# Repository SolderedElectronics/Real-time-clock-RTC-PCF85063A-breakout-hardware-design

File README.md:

# Real time clock RTC PCF85063A breakout Hardware Design

## About the Product

|  |
| :----------------------------------------------------------: |
| [Buy Real time clock RTC PCF85063A breakout](https://www.solde.red/333051) |

RTC (Real Time Clock) is a device that carefully and precisely tracks time and dates. It is extremely precise, so it is more suitable for long-term time tracking than clocks on microcontrollers. This breakout can work with an extremely low current and thanks to the alarm feature and interrupt pin, it will allow a microcontroller to enter sleep mode until its awaken by this RTC.

It has a built-in battery holder (battery not included) and even if power is lost, real-time tracking won’t be affected.

---

## Repository Contents

This repository contains all design files for Real time clock RTC PCF85063A breakout, organized as follows:

- **`CAD` folder**: Contains KiCAD design files, including:
  - Schematics
  - PCB layout
  - Panel PCB layout
  - Source 3D files in Fusion360, if any
  - All files are sorted by version with a detailed change log.
- **`OUTPUTS` folder**: Includes all production-ready files, such as:
  - Bill of Materials (BOM) and interactive BOM (iBOM)
  - PDF versions of schematics
  - 3D `.step` file of the board
  - 3D-printable models
  - Gerber files for PCB manufacturing
  - Image of the pinout of the board
  - Product image
  - Compliance, legal and generic sales documents

Refer to the `Change Log` in the CAD folder for details about updates between versions.

---

## Learn More About the Product

Beyond the repository, explore the following resources:

### Soldered Verify

The **Soldered Verify** system ensures every board you purchase from Soldered is fully functional. It also provides access to exclusive test data for your product. To get started, find the unique Soldered Verify ID on your product's packaging and enter the ID on the [Soldered Verify page](https://soldered.com/verify/) to access test results and additional product details.

### Soldered Community

Soldered Community is your go-to place for technical support. Our engineers track and answer all questions posted there, and it’s a great space for the maker community. Get answers to your questions and solutions for your challenges at [Soldered Community](https://soldered.com/community).

### solde.red

solde.red is an ultimate URL shortener and information hub. Access it by typing solde.red/ followed by your product SKU, e.g., [solde.red/333000](https://solde.red/333000), to find getting-started guides, datasheets, open-source hardware and software files, certifications, images, pinouts, and more. Read more about the shortener [here](https://solde.red/info/).

---

## Contributing

Contributions are welcome! Here’s how you can get involved:

- Submit pull requests to enhance the design or fix issues.
- Report bugs or problems by opening an issue.

We encourage community collaboration to make this product even better.

---

## About Soldered

[Soldered for Makers](https://soldered.com) specializes in designing and manufacturing electronic products tailored for enthusiasts, ranging from hobbyists to professionals. Our portfolio includes electronic boards, sensors, and actuators that are widely utilized in fields such as microelectronics, mechatronics, robotics, programming, and IoT. Every product we offer is designed in-house and built upon open-source hardware and software platforms. Proudly certified and manufactured within the European Union, our catalog likely includes the product you need for your project.

We complement these products with comprehensive tutorials and manuals, product descriptions, schematics, programming codes, and project examples. Our round-the-clock [customer and technical support](https://soldered.com/community) is available for all our products, irrespective of the sales channel. Soldered’s success and services reflect our maker community’s unwavering [trust](https://www.trustpilot.com/review/soldered.com), for which we are deeply grateful. Join our community and create using Soldered products.

---

## License

All Soldered open-source hardware (OSH) is under The TAPR Open Hardware License. Read more in the LICENSE file located in this repository.

**Disclaimer:**

No warranty - all designs in this repository are distributed in the hope that they will be useful, but without any warranty. They are provided "AS IS", therefore without warranty of any kind, either expressed or implied. The entire quality and performance of what you do with the contents of this repository are your responsibility. In no event Soldered Electronics will be liable for your damages, or losses, including any general, special, incidental, or consequential damage arising out of the use or inability to use the contents of this repository. 

---

## Have fun!

Thank you for your support from your fellow makers at Soldered Electronics.

Happy Making!

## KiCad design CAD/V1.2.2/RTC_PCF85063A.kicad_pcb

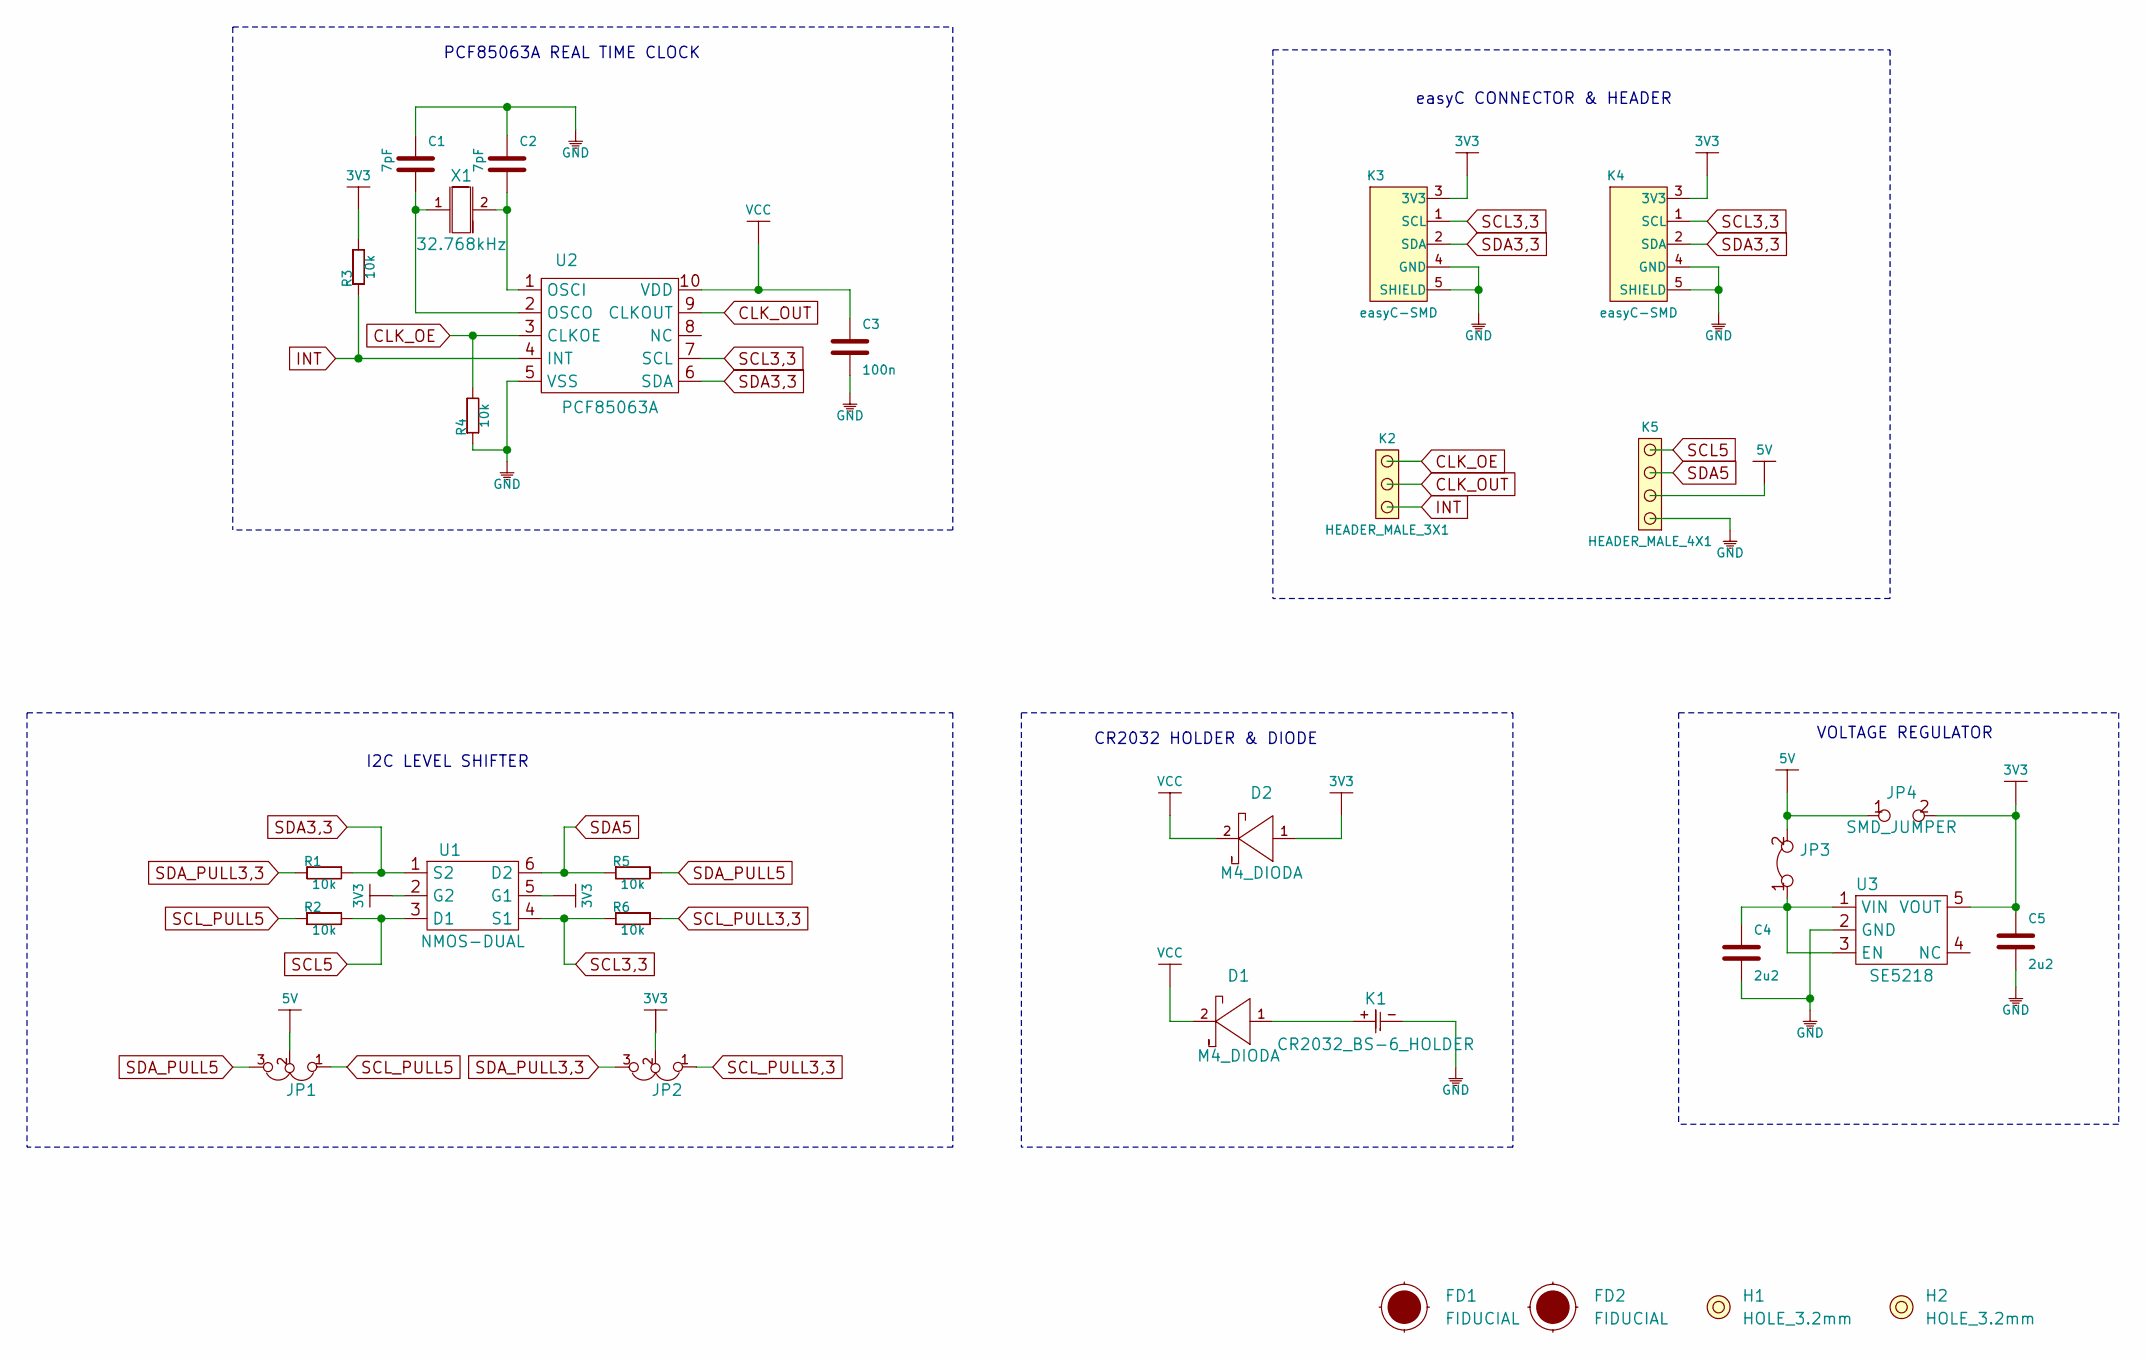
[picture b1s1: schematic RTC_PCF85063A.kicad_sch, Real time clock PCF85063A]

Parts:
C1, C2: 7pF; 0603C
C3: 100n; 0603C
C4, C5: 2u2; 0603C
D1, D2: M4_DIODA
FD1, FD2: FIDUCIAL; FIDUCIAL_23
H1, H2: HOLE_3.2mm
JP1, JP2: SMD_JUMPER_3_PAD_TRACE
JP3: SMD-JUMPER-CONNECTED_TRACE_SLODERMASK
JP4: SMD_JUMPER
K1: CR2032_BS-6_HOLDER; CR2032-BS-6-1
K2: HEADER_MALE_3X1
K3, K4: easyC-SMD; easyC-connector
K5: HEADER_MALE_4X1
R1, R2, R3, R4, R5, R6: 10k; 0603R
U1: NMOS-DUAL; SOT-363
U2: PCF85063A
U3: SE5218; SOT-23-5
X1: 32.768kHz; KRISTAL_3215

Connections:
3V3: C5.2, D2.1 (A), JP2.2, JP4.2, K3.3 (3V3), K4.3 (3V3), R3.2, U1.2 (G2), U1.5 (G1), U3.5 (VOUT)
5V: JP1.2, JP3.2, JP4.1, K5.2
CLK_OE: K2.3, R4.2, U2.3 (CLKOE)
CLK_OUT: K2.2, U2.9 (CLKOUT)
GND: C1.2, C2.2, C3.1, C4.1, C5.1, K1.-, K3.4 (GND), K3.5 (SHIELD), K4.4 (GND), K4.5 (SHIELD), K5.1, R4.1, U2.5 (VSS), U3.2 (GND)
INT: K2.1, R3.1, U2.4 (INT)
unnamed: C1.1, U2.2 (OSCO), X1.1
unnamed: C2.1, U2.1 (OSCI), X1.2
unnamed: C4.2, JP3.1, U3.1 (VIN), U3.3 (EN)
unnamed: D1.1 (A), K1.+
SCL3,3: K3.1 (SCL), K4.1 (SCL), R6.1, U1.4 (S1), U2.7 (SCL)
SCL5: K5.4, R2.2, U1.3 (D1)
SCL_PULL3,3: JP2.1, R6.2
SCL_PULL5: JP1.1, R2.1
SDA3,3: K3.2 (SDA), K4.2 (SDA), R1.2, U1.1 (S2), U2.6 (SDA)
SDA5: K5.3, R5.1, U1.6 (D2)
SDA_PULL3,3: JP2.3, R1.1
SDA_PULL5: JP1.3, R5.2
VCC: C3.2, D1.2 (K), D2.2 (K), U2.10 (VDD)

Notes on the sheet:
PCF85063A REAL TIME CLOCK
CR2032 HOLDER & DIODE
easyC CONNECTOR & HEADER
I2C LEVEL SHIFTER
VOLTAGE REGULATOR

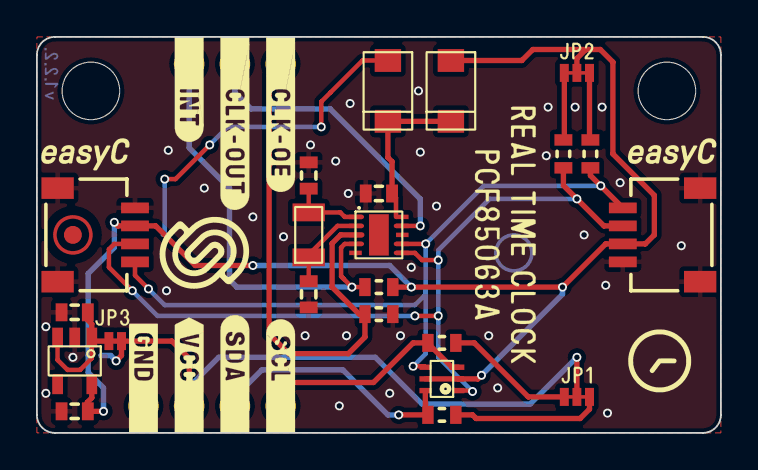
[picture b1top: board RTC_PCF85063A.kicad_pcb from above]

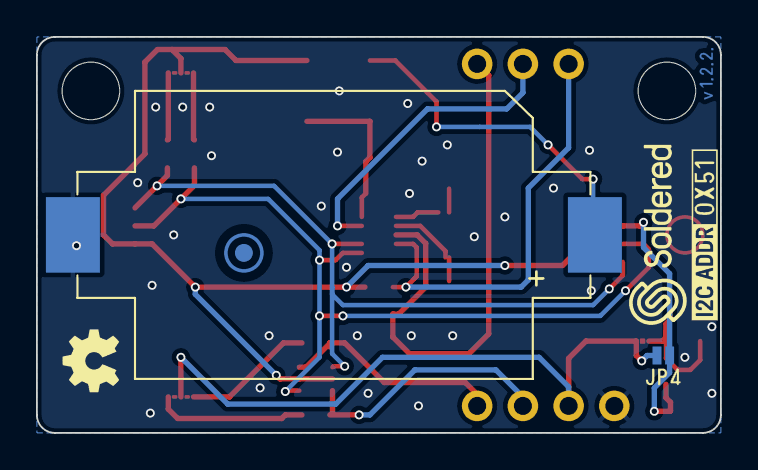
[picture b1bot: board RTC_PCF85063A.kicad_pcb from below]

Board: 2 copper layers, 38.0 x 22.0 mm, 30 parts (5 on the bottom side), 19 nets.

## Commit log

2022-08-06 Updating open source files.
